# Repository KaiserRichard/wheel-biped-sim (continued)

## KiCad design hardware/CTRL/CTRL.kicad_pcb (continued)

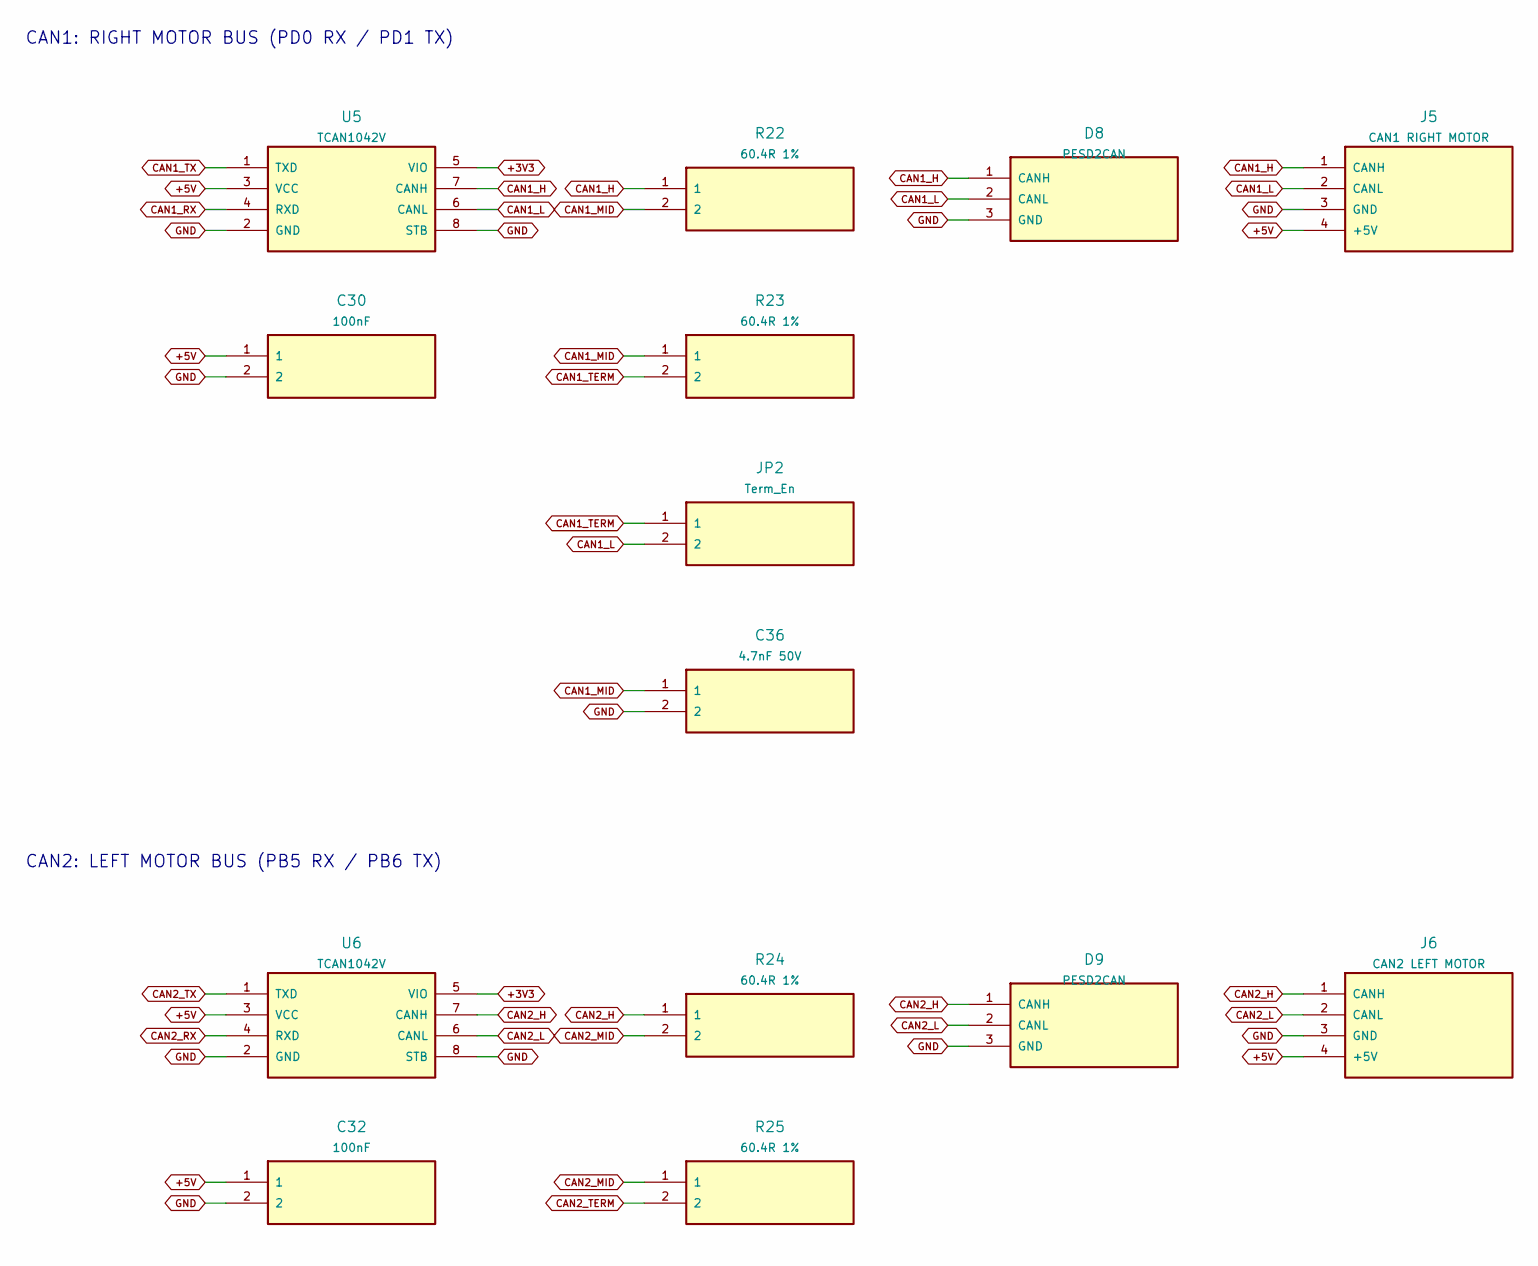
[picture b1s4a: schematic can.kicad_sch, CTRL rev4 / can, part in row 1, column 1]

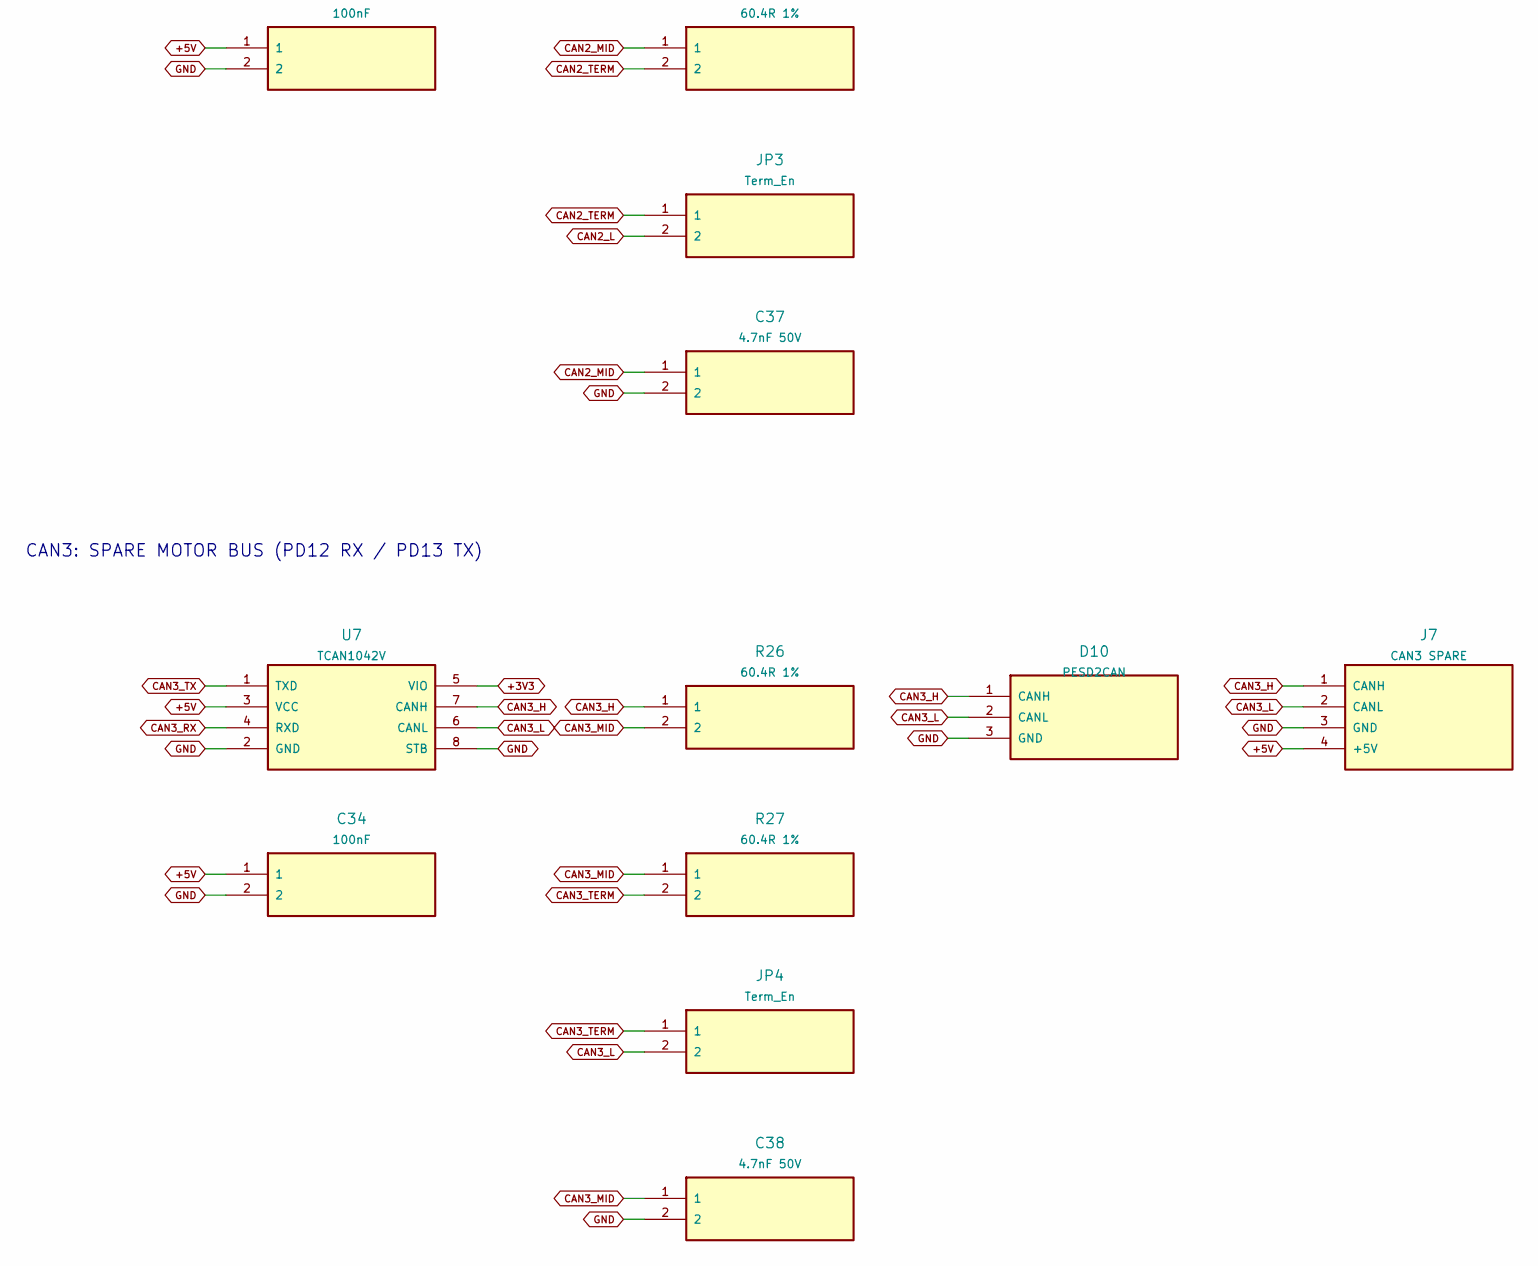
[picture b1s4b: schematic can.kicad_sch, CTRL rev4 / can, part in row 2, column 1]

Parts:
C30, C32, C34: 100nF; C_0805_2012Metric
C36, C37, C38: 4.7nF 50V; C_0805_2012Metric
D8, D9, D10: PESD2CAN; SOT-23
J5: CAN1 RIGHT MOTOR; Molex_Micro-Fit_3.0_43045-0400_2x02_P3.00mm_Horizontal
J6: CAN2 LEFT MOTOR; Molex_Micro-Fit_3.0_43045-0400_2x02_P3.00mm_Horizontal
J7: CAN3 SPARE; Molex_Micro-Fit_3.0_43045-0400_2x02_P3.00mm_Horizontal
JP2, JP3, JP4: Term_En; PinHeader_1x02_P2.54mm_Vertical
R22, R23, R24, R25, R26, R27: 60.4R 1%; R_0805_2012Metric
U5, U6, U7: TCAN1042V; SOIC-8_3.9x4.9mm_P1.27mm

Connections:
+3V3: U5.5 (VIO), U6.5 (VIO), U7.5 (VIO); also elsewhere on the board
+5V: C30.1, C32.1, C34.1, J5.4 (+5V), J6.4 (+5V), J7.4 (+5V), U5.3 (VCC), U6.3 (VCC), U7.3 (VCC); also elsewhere on the board
CAN1_H: D8.1 (CANH), J5.1 (CANH), R22.1, U5.7 (CANH)
CAN1_L: D8.2 (CANL), J5.2 (CANL), JP2.2, U5.6 (CANL)
CAN1_MID: C36.1, R22.2, R23.1
CAN1_RX: U5.4 (RXD); also elsewhere on the board
CAN1_TERM: JP2.1, R23.2
CAN1_TX: U5.1 (TXD); also elsewhere on the board
CAN2_H: D9.1 (CANH), J6.1 (CANH), R24.1, U6.7 (CANH)
CAN2_L: D9.2 (CANL), J6.2 (CANL), JP3.2, U6.6 (CANL)
CAN2_MID: C37.1, R24.2, R25.1
CAN2_RX: U6.4 (RXD); also elsewhere on the board
CAN2_TERM: JP3.1, R25.2
CAN2_TX: U6.1 (TXD); also elsewhere on the board
CAN3_H: D10.1 (CANH), J7.1 (CANH), R26.1, U7.7 (CANH)
CAN3_L: D10.2 (CANL), J7.2 (CANL), JP4.2, U7.6 (CANL)
CAN3_MID: C38.1, R26.2, R27.1
CAN3_RX: U7.4 (RXD); also elsewhere on the board
CAN3_TERM: JP4.1, R27.2
CAN3_TX: U7.1 (TXD); also elsewhere on the board
GND: C30.2, C32.2, C34.2, C36.2, C37.2, C38.2, D8.3 (GND), D9.3 (GND), D10.3 (GND), J5.3 (GND), J6.3 (GND), J7.3 (GND), U5.2 (GND), U5.8 (STB), U6.2 (GND), U6.8 (STB), U7.2 (GND), U7.8 (STB); also elsewhere on the board

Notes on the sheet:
CAN1: RIGHT MOTOR BUS (PD0 RX / PD1 TX)
CAN2: LEFT MOTOR BUS (PB5 RX / PB6 TX)
CAN3: SPARE MOTOR BUS (PD12 RX / PD13 TX)

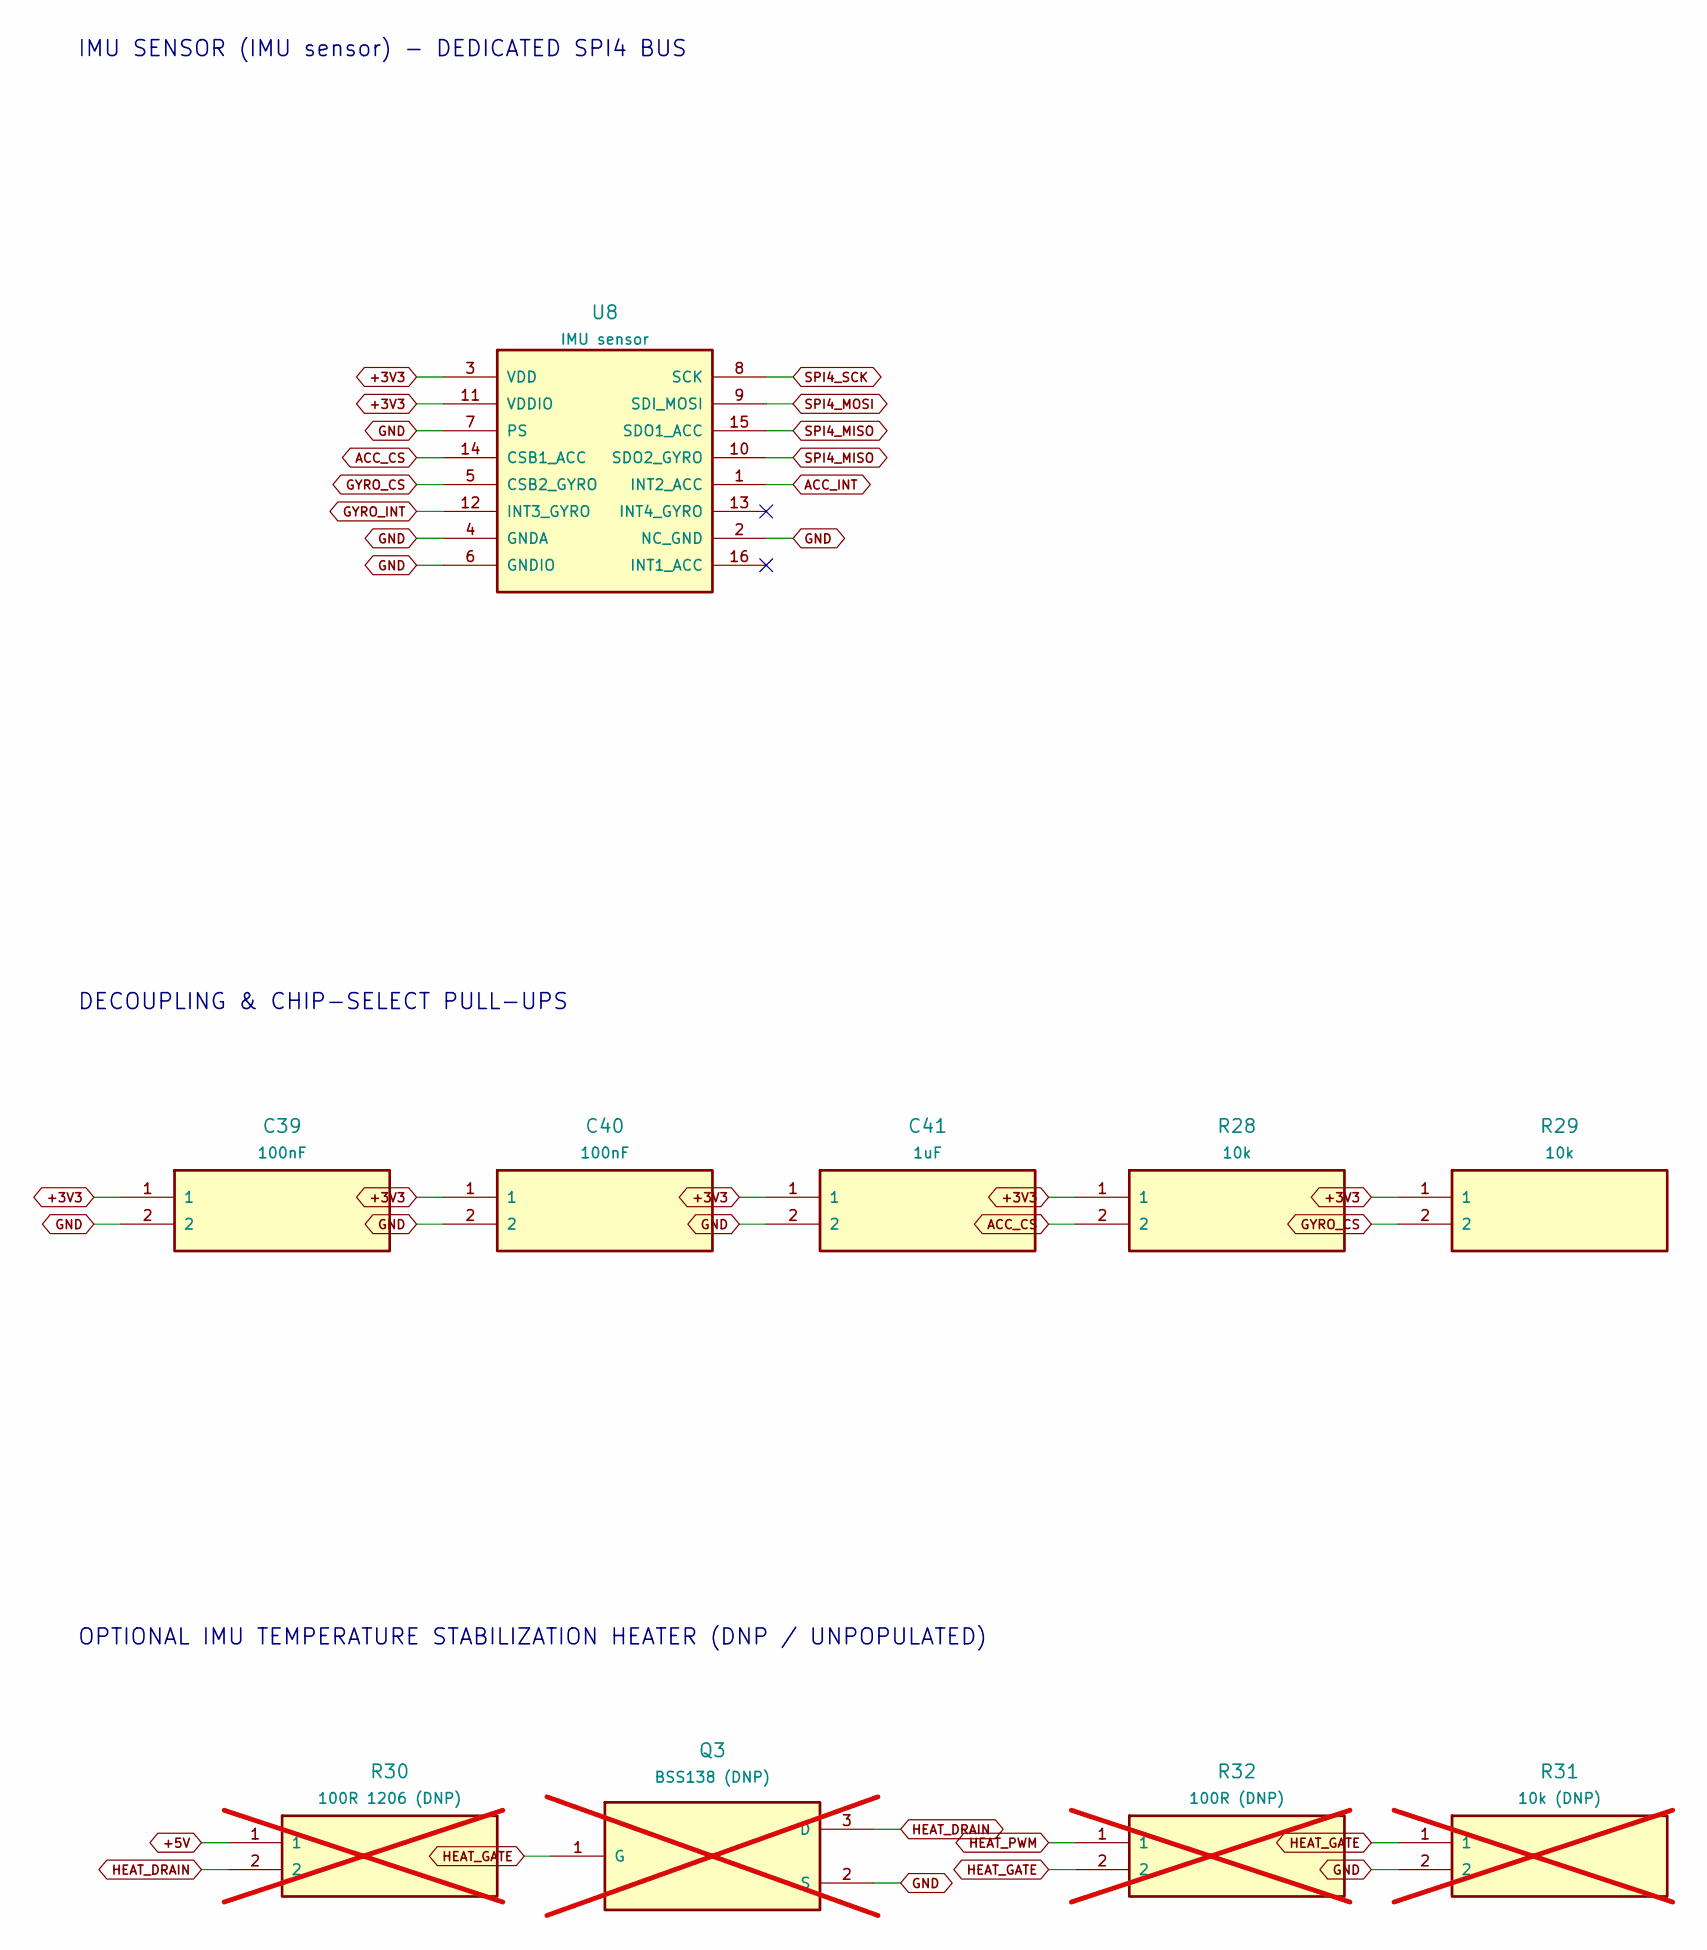
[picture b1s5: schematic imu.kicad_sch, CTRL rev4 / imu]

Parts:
C39, C40: 100nF; C_0805_2012Metric
C41: 1uF; C_0805_2012Metric
Q3: BSS138 (DNP); SOT-23; not fitted
R28, R29: 10k; R_0805_2012Metric
R30: 100R 1206 (DNP); R_1206_3216Metric; not fitted
R31: 10k (DNP); R_0805_2012Metric; not fitted
R32: 100R (DNP); R_0805_2012Metric; not fitted
U8: IMU sensor; IMU_sensor_LGA16

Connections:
+3V3: C39.1, C40.1, C41.1, R28.1, R29.1, U8.3 (VDD), U8.11 (VDDIO); also elsewhere on the board
+5V: R30.1; also elsewhere on the board
ACC_CS: R28.2, U8.14 (CSB1_ACC); also elsewhere on the board
ACC_INT: U8.1 (INT2_ACC); also elsewhere on the board
GND: C39.2, C40.2, C41.2, Q3.2 (S), R31.2, U8.2 (NC_GND), U8.4 (GNDA), U8.6 (GNDIO), U8.7 (PS); also elsewhere on the board
GYRO_CS: R29.2, U8.5 (CSB2_GYRO); also elsewhere on the board
GYRO_INT: U8.12 (INT3_GYRO); also elsewhere on the board
HEAT_DRAIN: Q3.3 (D), R30.2
HEAT_GATE: Q3.1 (G), R31.1, R32.2
HEAT_PWM: R32.1; also elsewhere on the board
SPI4_MISO: U8.10 (SDO2_GYRO), U8.15 (SDO1_ACC); also elsewhere on the board
SPI4_MOSI: U8.9 (SDI_MOSI); also elsewhere on the board
SPI4_SCK: U8.8 (SCK); also elsewhere on the board

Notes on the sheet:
IMU SENSOR (IMU sensor) - DEDICATED SPI4 BUS
DECOUPLING & CHIP-SELECT PULL-UPS
OPTIONAL IMU TEMPERATURE STABILIZATION HEATER (DNP / UNPOPULATED)

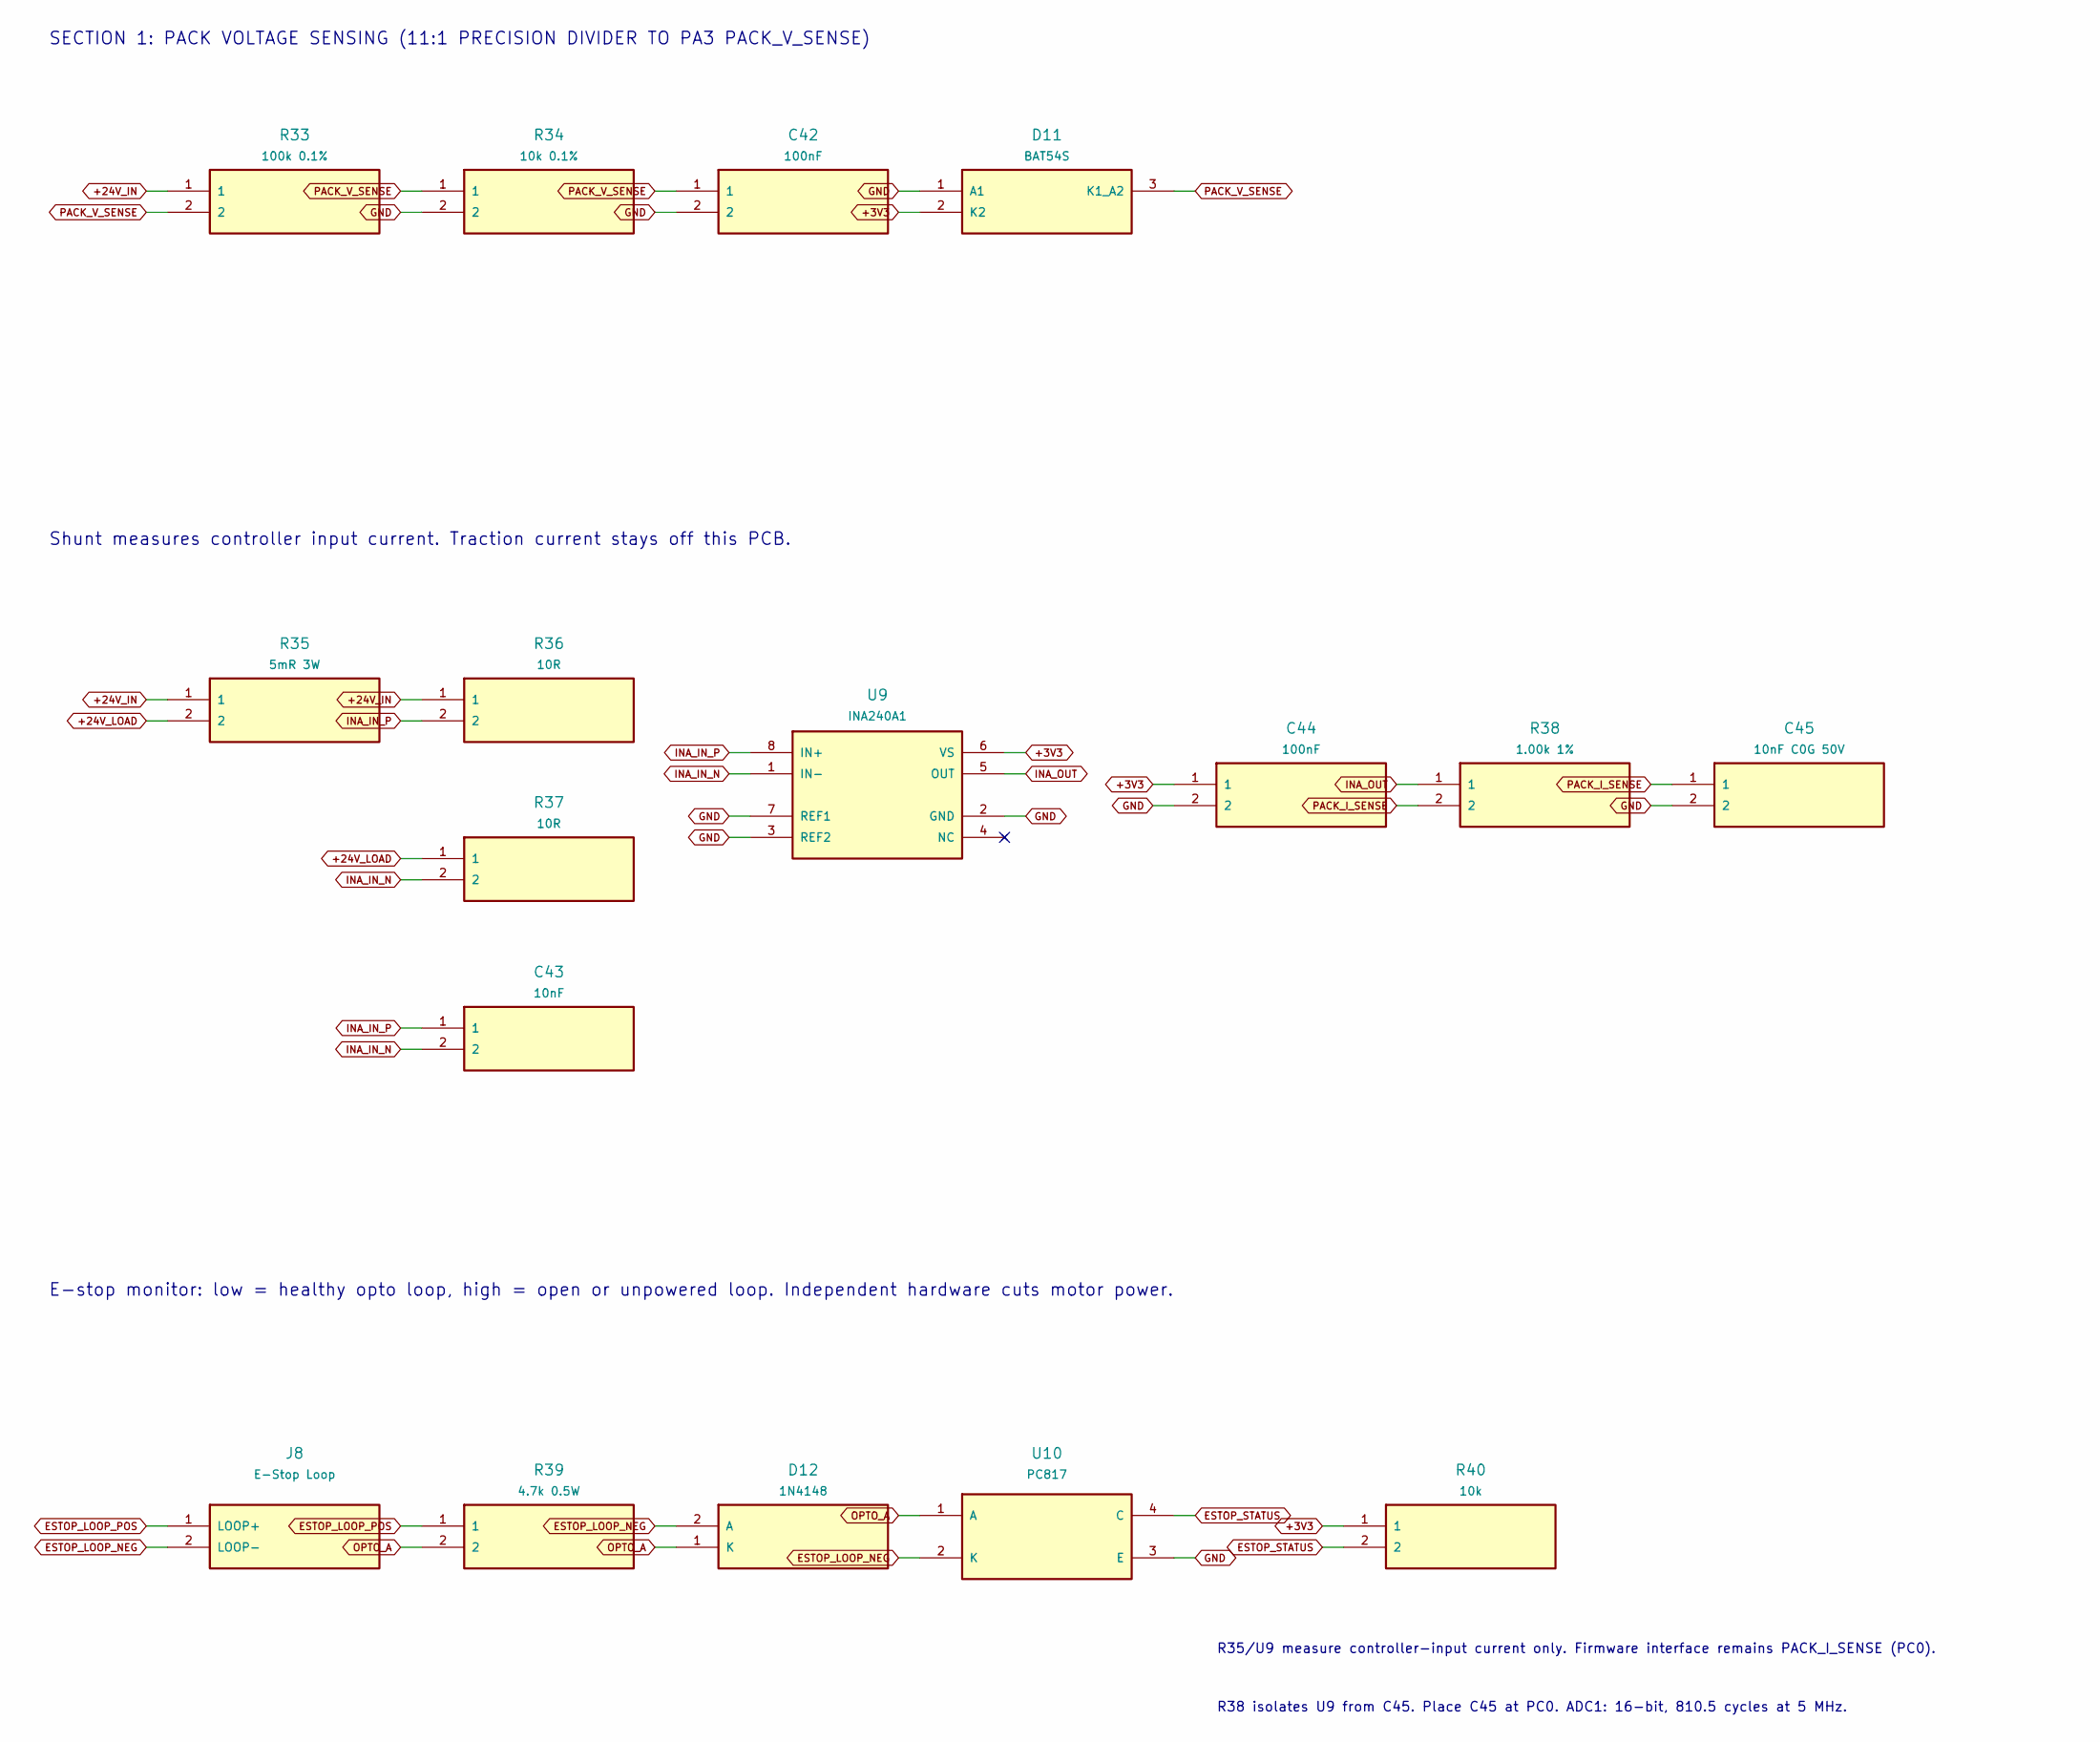
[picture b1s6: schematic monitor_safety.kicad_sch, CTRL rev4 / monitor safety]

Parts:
C42, C44: 100nF; C_0805_2012Metric
C43: 10nF; C_0805_2012Metric
C45: 10nF C0G 50V; C_0805_2012Metric
D11: BAT54S; SOT-23
D12: 1N4148; D_SOD-123
J8: E-Stop Loop; PinHeader_1x02_P2.54mm_Vertical
R33: 100k 0.1%; R_0805_2012Metric
R34: 10k 0.1%; R_0805_2012Metric
R35: 5mR 3W; R_2512_6332Metric
R36, R37: 10R; R_0805_2012Metric
R38: 1.00k 1%; R_0805_2012Metric
R39: 4.7k 0.5W; R_2512_6332Metric
R40: 10k; R_0805_2012Metric
U9: INA240A1; SOIC-8_3.9x4.9mm_P1.27mm
U10: PC817; SO-4_4.4x3.6mm_P2.54mm

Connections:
+3V3: C44.1, D11.2 (K2), R40.1, U9.6 (VS); also elsewhere on the board
+24V_IN: R33.1, R35.1, R36.1; also elsewhere on the board
+24V_LOAD: R35.2, R37.1; also elsewhere on the board
ESTOP_LOOP_NEG: D12.2 (A), J8.2 (LOOP-), U10.2 (K)
ESTOP_LOOP_POS: J8.1 (LOOP+), R39.1
ESTOP_STATUS: R40.2, U10.4 (C); also elsewhere on the board
GND: C42.2, C44.2, C45.2, D11.1 (A1), R34.2, U9.2 (GND), U9.3 (REF2), U9.7 (REF1), U10.3 (E); also elsewhere on the board
INA_IN_N: C43.2, R37.2, U9.1 (IN-)
INA_IN_P: C43.1, R36.2, U9.8 (IN+)
INA_OUT: R38.1, U9.5 (OUT)
OPTO_A: D12.1 (K), R39.2, U10.1 (A)
PACK_I_SENSE: C45.1, R38.2; also elsewhere on the board
PACK_V_SENSE: C42.1, D11.3 (K1_A2), R33.2, R34.1; also elsewhere on the board

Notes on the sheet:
SECTION 1: PACK VOLTAGE SENSING (11:1 PRECISION DIVIDER TO PA3 PACK_V_SENSE)
Shunt measures controller input current. Traction current stays off this PCB.
E-stop monitor: low = healthy opto loop, high = open or unpowered loop. Independent hardware cuts motor power.
R35/U9 measure controller-input current only. Firmware interface remains PACK_I_SENSE (PC0).
R38 isolates U9 from C45. Place C45 at PC0. ADC1: 16-bit, 810.5 cycles at 5 MHz.

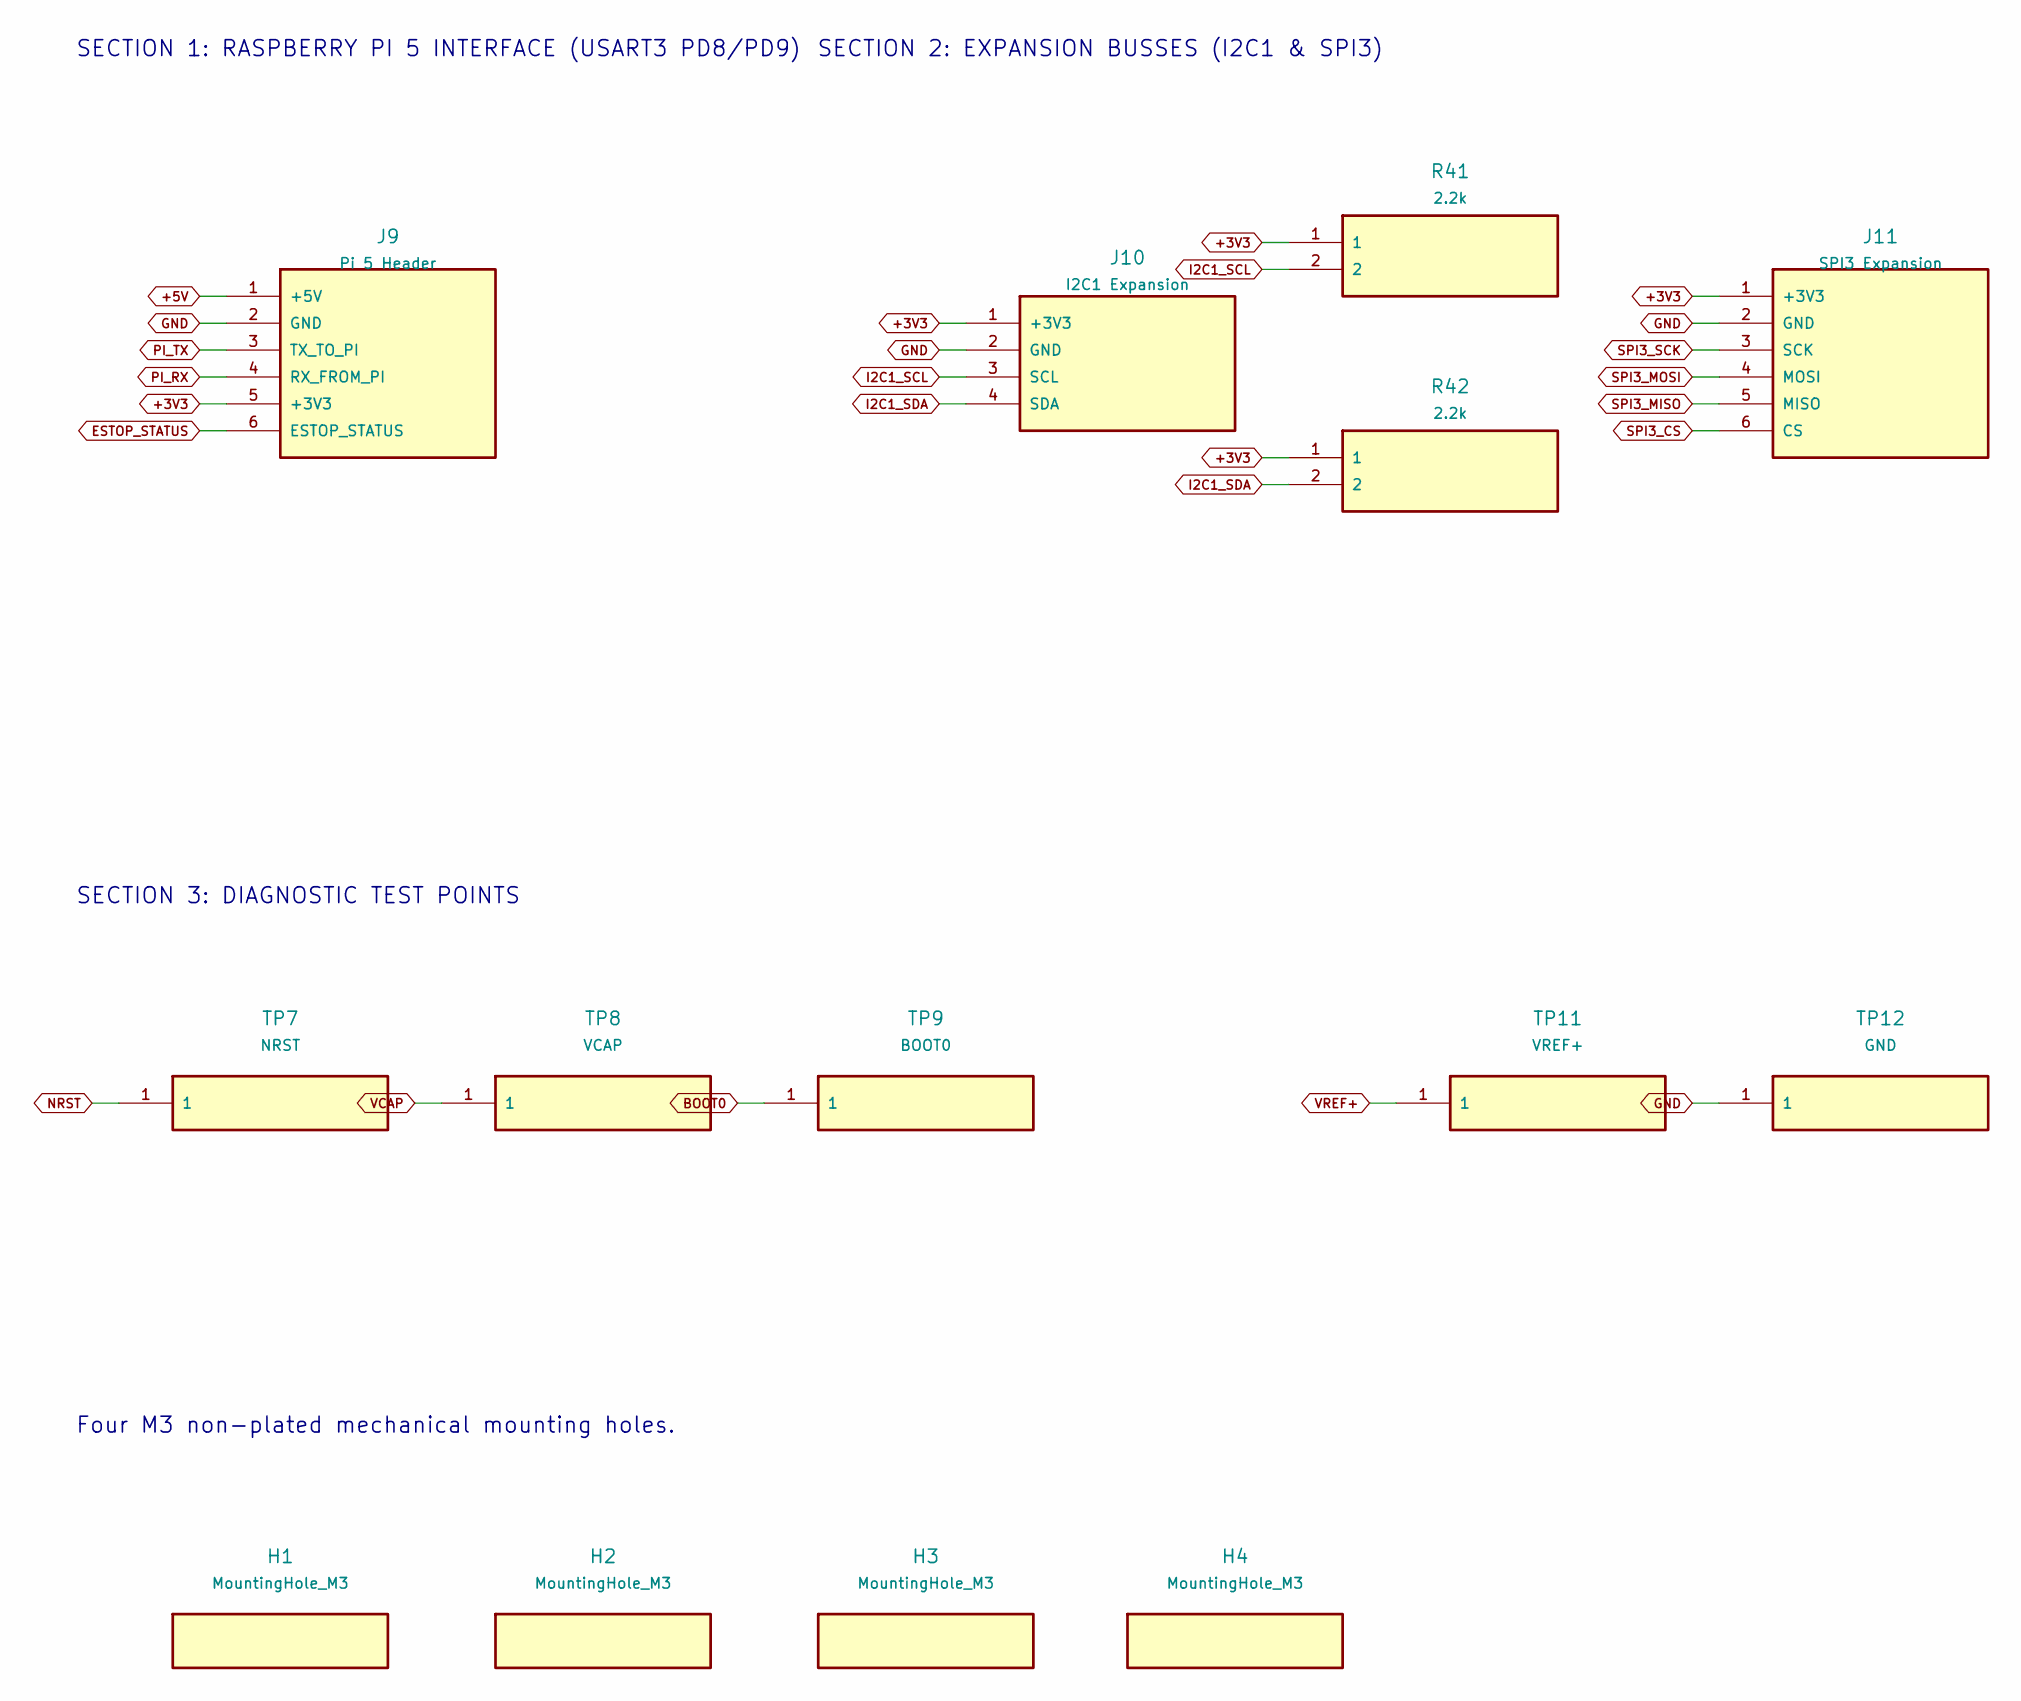
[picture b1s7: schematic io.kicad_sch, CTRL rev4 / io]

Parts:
H1, H2, H3, H4: MountingHole_M3; MountingHole_3.2mm_M3
J9: Pi 5 Header; PinHeader_1x06_P2.54mm_Vertical
J10: I2C1 Expansion; PinHeader_1x04_P2.54mm_Vertical
J11: SPI3 Expansion; PinHeader_1x06_P2.54mm_Vertical
R41, R42: 2.2k; R_0805_2012Metric
TP7: NRST; TestPoint_Pad_D1.5mm
TP8: VCAP; TestPoint_Pad_D1.0mm
TP9: BOOT0; TestPoint_Pad_D1.5mm
TP11: VREF+; TestPoint_Pad_D1.5mm
TP12: GND; TestPoint_Pad_D1.5mm

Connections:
+3V3: J9.5 (+3V3), J10.1 (+3V3), J11.1 (+3V3), R41.1, R42.1; also elsewhere on the board
+5V: J9.1 (+5V); also elsewhere on the board
BOOT0: TP9.1; also elsewhere on the board
ESTOP_STATUS: J9.6 (ESTOP_STATUS); also elsewhere on the board
GND: J9.2 (GND), J10.2 (GND), J11.2 (GND), TP12.1; also elsewhere on the board
I2C1_SCL: J10.3 (SCL), R41.2; also elsewhere on the board
I2C1_SDA: J10.4 (SDA), R42.2; also elsewhere on the board
NRST: TP7.1; also elsewhere on the board
PI_RX: J9.4 (RX_FROM_PI); also elsewhere on the board
PI_TX: J9.3 (TX_TO_PI); also elsewhere on the board
SPI3_CS: J11.6 (CS); also elsewhere on the board
SPI3_MISO: J11.5 (MISO); also elsewhere on the board
SPI3_MOSI: J11.4 (MOSI); also elsewhere on the board
SPI3_SCK: J11.3 (SCK); also elsewhere on the board
VCAP: TP8.1; also elsewhere on the board
VREF+: TP11.1; also elsewhere on the board

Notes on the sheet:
SECTION 1: RASPBERRY PI 5 INTERFACE (USART3 PD8/PD9)
SECTION 2: EXPANSION BUSSES (I2C1 & SPI3)
SECTION 3: DIAGNOSTIC TEST POINTS
Four M3 non-plated mechanical mounting holes.
